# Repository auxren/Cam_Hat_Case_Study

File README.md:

# Raspberry Pi Zero 2 W Camera Module Daughterboard

## Overview

This was from a 72hr design challenge / case study for an interview for a Senior Electrical Engineering Role.

## Requirements

- Camera Module: Integrate the IMX219 camera module (IQL-IMX219/FF).
= Motion Detection: Integrate a suitable PIR motion sensor to detect motion to trigger the
camera.
- Lighting Adjustment: Integrate a suitable ambient light sensor that will be later used to
adjust camera settings based on lighting conditions.
- Power Supply: Design a power supply circuit to ensure stable operation. Choose and
justify the power management components used. Use at least one switching regulator in
your design.
- Form Factor: Ensure the daughter board fits within the dimensions of the Raspberry Pi
Zero 2 W (65mm x 30mm).
- Interconnection: The daughter board will connect to the Raspberry Pi Zero 2 W through
the GPIO header. All components, including the camera module, PIR sensor, and
ambient light sensor, must be placed on the daughter board. Additionally, include an FFC
connector on the edge of the daughter board to allow the user to connect an FFC cable
between the daughter board and the CSI interface of the Raspberry Pi Zero W.
- Power Supply: Assume the Raspberry Pi will be powered with a 5V 3A DC power
supply. Consider power losses and efficiencies.

## Features

- IMX219 camera integration via CSI interface  
- Ambient light sensor for lighting-aware imaging  
- PIR motion sensor to trigger camera events  
- Switching regulator-based power supply for high efficiency  
- Direct connection to the Raspberry Pi via GPIO and FFC  
- Test points and layout considerations for testability

## System Requirements

| Component              | Specification                                                  |
|------------------------|----------------------------------------------------------------|
| Camera Module          | IMX219 (IQL-IMX219/FF)                                         |
| PIR Sensor             | Selected for compact form factor and reliable motion detection |
| Ambient Light Sensor   | Tuned for visible spectrum and camera exposure control         |
| Power Input            | 5V 3A DC (via Raspberry Pi USB input)                          |
| Form Factor            | 65mm x 30mm (same as Raspberry Pi Zero 2 W)                    |
| Interfaces             | GPIO header and FFC connector                                  |

## Deliverables

- ✅ Schematic Design (KiCad project and PDF)
- ✅ PCB Layout (KiCad, Gerber files, and 3D model)
- ✅ Bill of Materials (BOM) with part numbers and specifications
- ✅ Power Supply Design Document (efficiency and regulator choice justification)
- ✅ Design Decision Documentation (component selection and rationale)

## Folder Structure

<pre> <code>
├── Cam_Hat_Case_Study_Oren_Levy_Presentation.key -- Case study presentation. Open in Apple Keynote.
├── Cam_Hat_Case_Study_Oren_Levy_Presentation.pdf
├── Firmware:Software
│   └── TfH_Case_Study_FW_TODO.numbers -- Document for tracking items FW should be mindful of. Open in Apple Numbers.
├── Hardware
│   ├── Block Diagram
│   │   └── Cam_Hat_Case_Study_Block_Diagram.png -- High level block diagram
│   ├── BOMs
│   │   └── Cam_Hat_Case_Study_PCB_Assembly_BOM.csv -- Assembly BOM
│   ├── Datasheets -- Datasheet PDFs for referencing
│   ├── Pinout Docs
│   │   └── Cam_Hat_Case_Study_Pinout_Tracker.numbers -- Document for tracking pinouts and net names. Open in Apple Numbers.
│   ├── Power
│   │   └── CamHat_Power_Tracker.numbers -- Power calculator document. Open in Apple Numbers.
│   ├── Schematic
│   │   └── Cam_Hat_Case_Study_Schematic.pdf
│   └── TfH_Case_Study -- KiCad Project
├── LICENSE
├── Mechanical
│   ├── Cam_Hat_Case_Study_Model.STEP -- Model of full "product"
│   ├── Cam_Hat_Case_Study_Ortho_Render.png
│   ├── Cam_Hat_Case_Study_Render_Case_Ortho.png
│   ├── Cam_Hat_Case_Study_Side_Render.png
│   └── Subassemblies  -- Folder with dxf and stp files used for assembly
└── README.md
</code> </pre>

## Block Diagram

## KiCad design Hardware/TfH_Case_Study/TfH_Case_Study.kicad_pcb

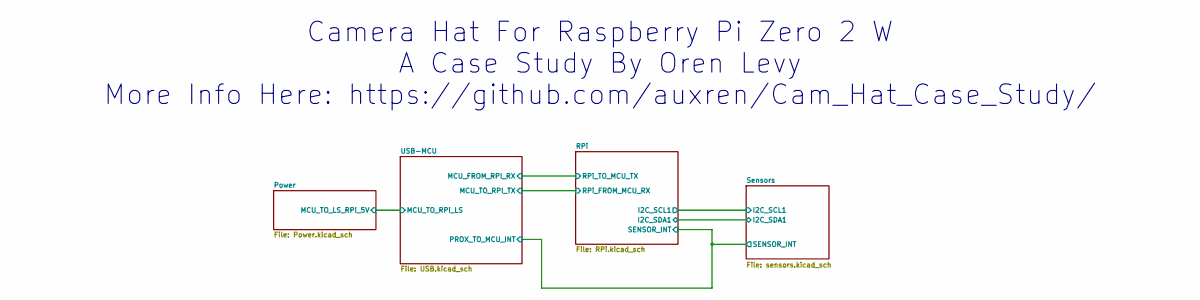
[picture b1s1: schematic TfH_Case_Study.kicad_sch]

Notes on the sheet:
Camera Hat For Raspberry Pi Zero 2 W A Case Study By Oren Levy More Info Here: https://github.com/auxren/Cam_Hat_Case_Study/

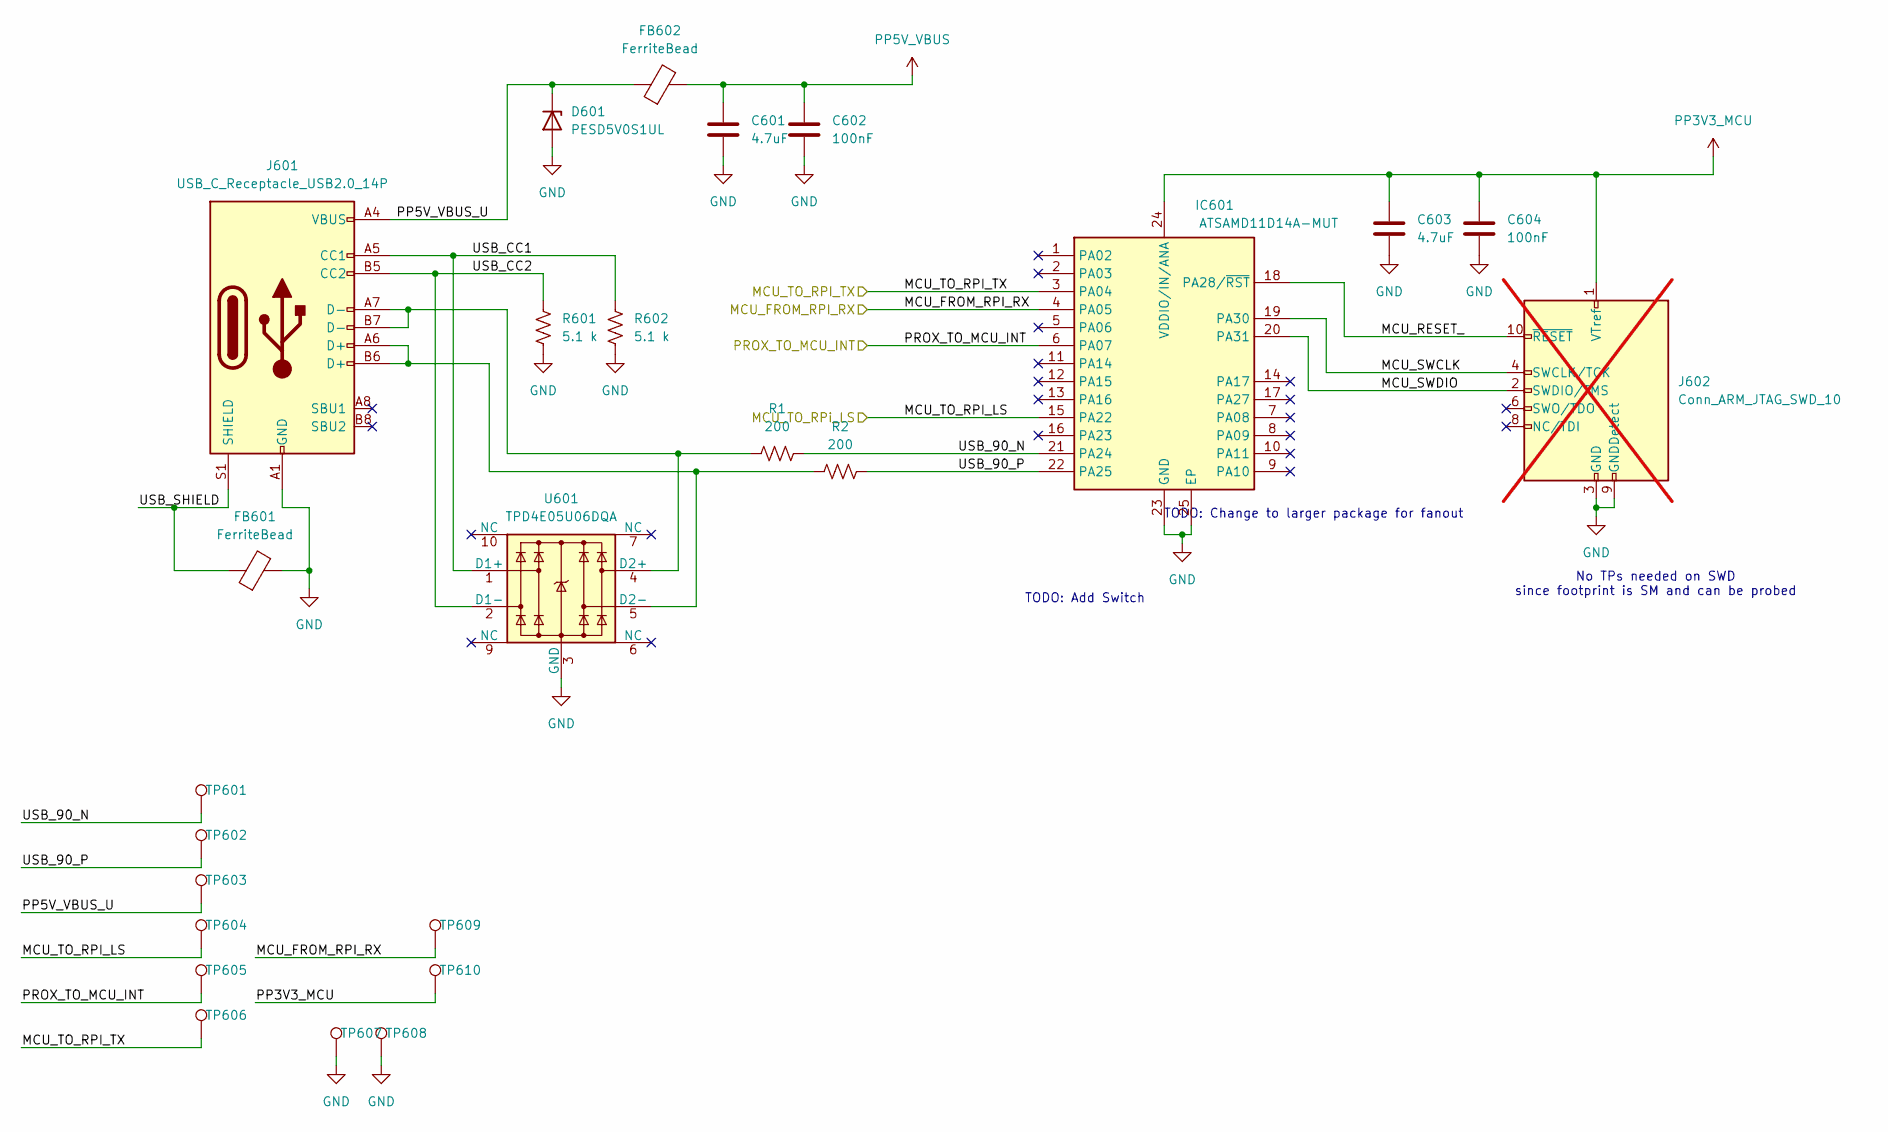
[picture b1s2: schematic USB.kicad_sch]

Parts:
C601, C603: 4.7uF; C_0402_1005Metric
C602, C604: 100nF; C_0402_1005Metric
D601: PESD5V0S1UL; D_SOD-882
FB601, FB602: FerriteBead; C_0402_1005Metric
IC601: ATSAMD11D14A-MUT; QFN50P400X400X90-25N-D; Mouser Part Number 556-ATSAMD11D14A-MUT
J601: USB_C_Receptacle_USB2.0_14P; USB_C_Receptacle_GCT_USB4105-xx-A_16P_TopMnt_Horizontal
J602: Conn_ARM_JTAG_SWD_10; PinHeader_2x05_P1.00mm_Vertical_SMD; not fitted
R1, R2: 200; R_0402_1005Metric
R601, R602: 5.1 k; R_0402_1005Metric
TP601, TP602, TP603, TP604, TP605, TP606, TP607, TP608, TP609, TP610: TestPoint; TestPoint_Pad_D1.5mm
U601: TPD4E05U06DQA; USON-10_2.5x1.0mm_P0.5mm

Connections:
/Sensors/SENSOR_INT: IC601.6 (PA07), TP605.1; also elsewhere on the board
/USB-MCU/MCU_FROM_RPI_RX: IC601.4 (PA05), TP609.1; also elsewhere on the board
/USB-MCU/MCU_RESET_: IC601.18 (PA28/~RST), J602.10 (~RESET)
/USB-MCU/MCU_SWCLK: IC601.19 (PA30), J602.4 (SWCLK/TCK)
/USB-MCU/MCU_SWDIO: IC601.20 (PA31), J602.2 (SWDIO/TMS)
/USB-MCU/MCU_TO_RPI_LS: IC601.15 (PA22), TP604.1; also elsewhere on the board
/USB-MCU/MCU_TO_RPI_TX: IC601.3 (PA04), TP606.1; also elsewhere on the board
/USB-MCU/PP5V_VBUS_U: D601.1 (K), FB602.1, J601.A4 (VBUS), J601.A9 (VBUS), J601.B4 (VBUS), J601.B9 (VBUS), TP603.1
/USB-MCU/USB_CC1: J601.A5 (CC1), R602.1, U601.1 (D1+)
/USB-MCU/USB_CC2: J601.B5 (CC2), R601.1, U601.2 (D1-)
/USB-MCU/USB_SHIELD: FB601.1, J601.S1 (SHIELD)
GND: C601.2, C602.2, C603.2, C604.2, D601.2 (A), FB601.2, IC601.23 (GND), IC601.25 (EP), J601.A1 (GND), J601.A12 (GND), J601.B1 (GND), J601.B12 (GND), J602.3 (GND), J602.5 (GND), J602.9 (GNDDetect), R601.2, R602.2, TP607.1, TP608.1, U601.3 (GND), U601.8 (GND); also elsewhere on the board
PP3V3_MCU: C603.1, C604.1, IC601.24 (VDDIO/IN/ANA), J602.1 (VTref), TP610.1; also elsewhere on the board
PP5V_VBUS: C601.1, C602.1, FB602.2; also elsewhere on the board

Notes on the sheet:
No TPs needed on SWD since footprint is SM and can be probed
TODO: Change to larger package for fanout
TODO: Add Switch

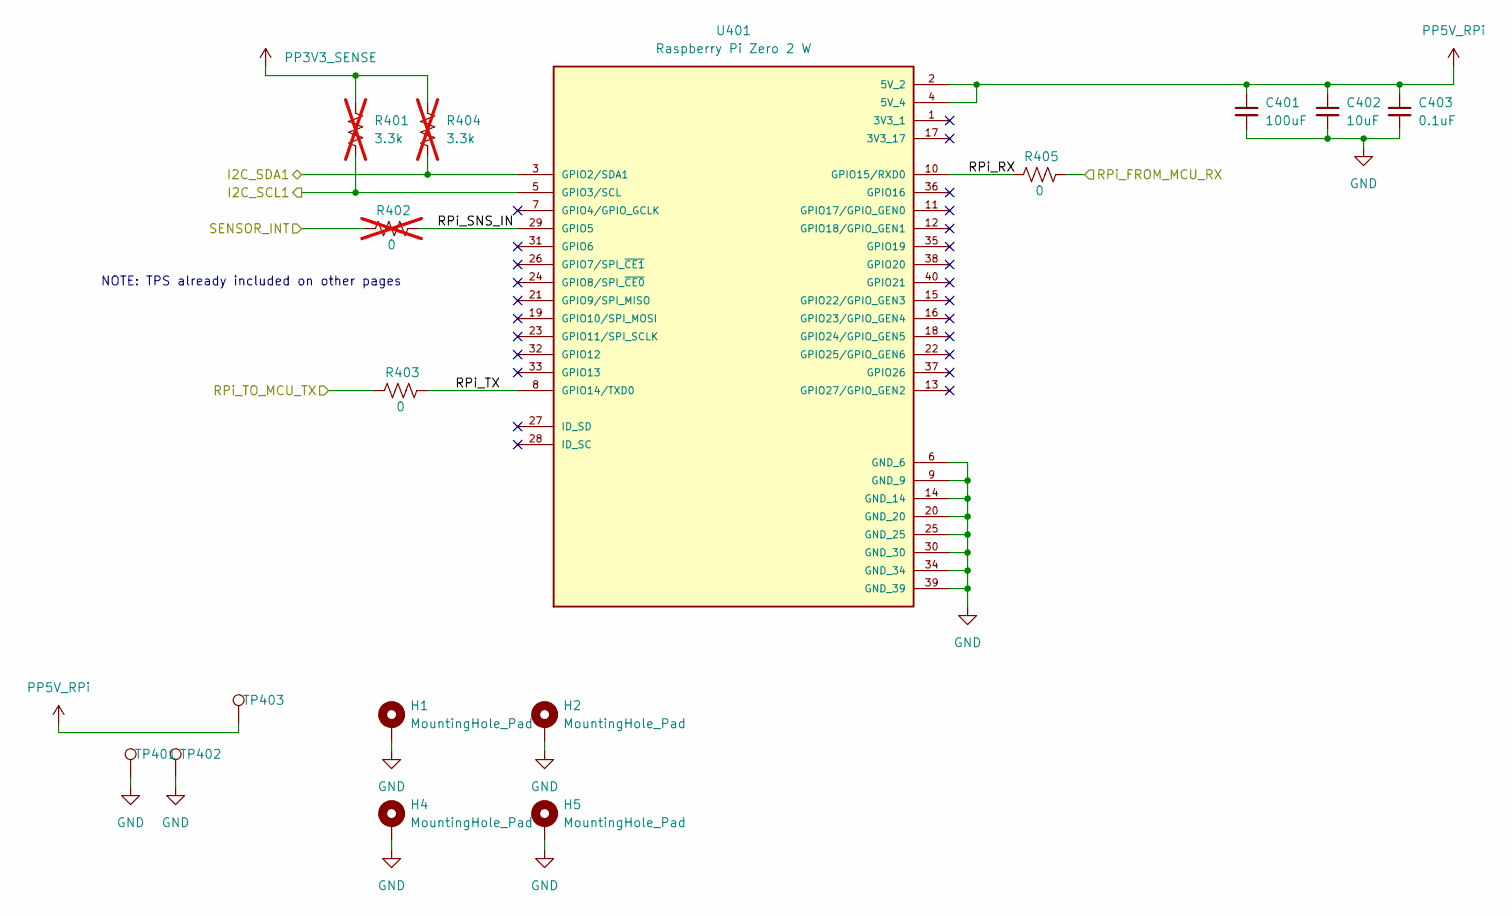
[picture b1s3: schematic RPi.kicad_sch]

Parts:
C401: 100uF; C_0603_1608Metric
C402: 10uF; C_0603_1608Metric
C403: 0.1uF; C_0402_1005Metric
H1, H2, H4, H5: MountingHole_Pad; MountingHole_3.2mm_M3_DIN965_Pad
R401, R404: 3.3k; C_0402_1005Metric; not fitted
R402: 0; C_0402_1005Metric; not fitted
R403, R405: 0; C_0402_1005Metric
TP401, TP402, TP403: TestPoint; TestPoint_Pad_D1.5mm
U401: Raspberry Pi Zero 2 W; PinHeader_2x20_P2.54mm_Vertical; PARTREV April 2024

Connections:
/RPi/RPi_RX: R405.1, U401.10 (GPIO15/RXD0)
/RPi/RPi_SNS_IN: R402.2, U401.29 (GPIO5)
/RPi/RPi_TX: R403.2, U401.8 (GPIO14/TXD0)
/Sensors/I2C_SCL1: R401.2, U401.5 (GPIO3/SCL); also elsewhere on the board
/Sensors/I2C_SDA1: R404.2, U401.3 (GPIO2/SDA1); also elsewhere on the board
/Sensors/SENSOR_INT: R402.1; also elsewhere on the board
/USB-MCU/MCU_FROM_RPI_RX: R403.1; also elsewhere on the board
/USB-MCU/MCU_TO_RPI_TX: R405.2; also elsewhere on the board
GND: C401.2, C402.2, C403.2, H1.1, H2.1, H4.1, H5.1, TP401.1, TP402.1, U401.6 (GND_6), U401.9 (GND_9), U401.14 (GND_14), U401.20 (GND_20), U401.25 (GND_25), U401.30 (GND_30), U401.34 (GND_34), U401.39 (GND_39); also elsewhere on the board
PP3V3_SENSE: R401.1, R404.1; also elsewhere on the board
PP5V_RPi: C401.1, C402.1, C403.1, TP403.1, U401.2 (5V_2), U401.4 (5V_4); also elsewhere on the board

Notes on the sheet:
NOTE: TPS already included on other pages

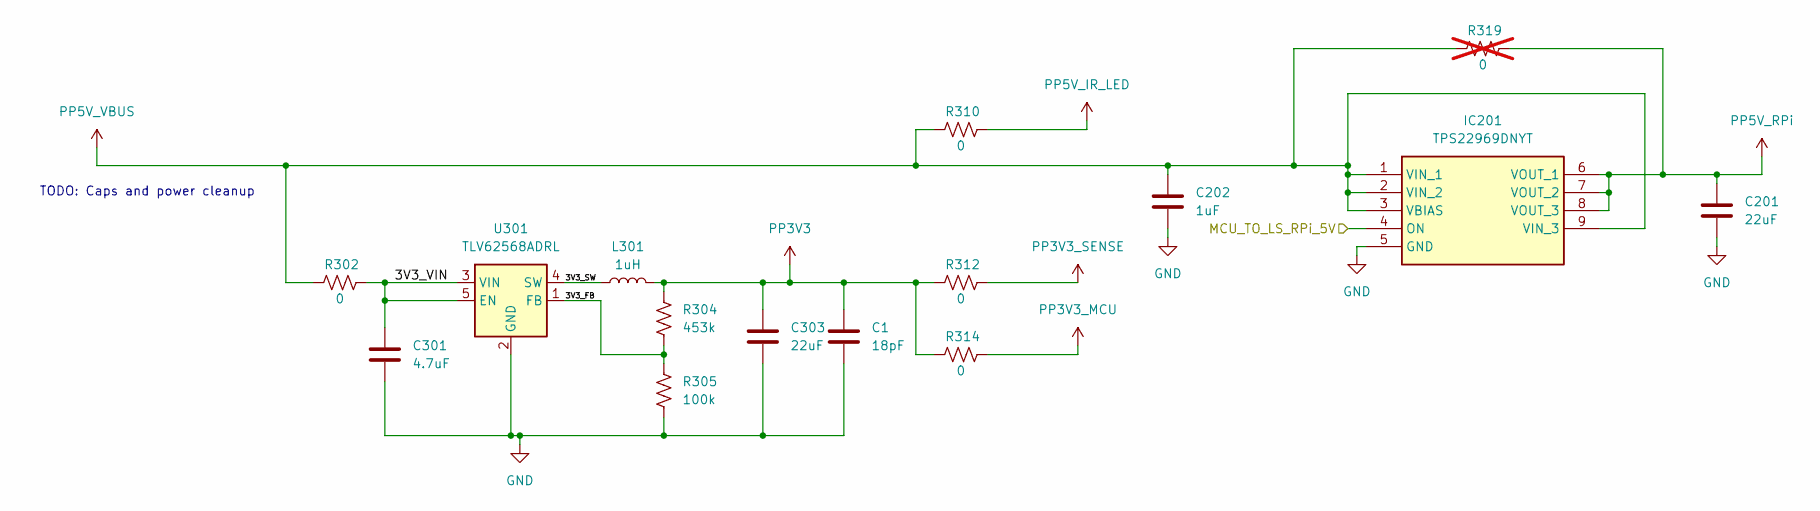
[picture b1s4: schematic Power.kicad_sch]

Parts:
C1: 18pF; C_0402_1005Metric
C201, C303: 22uF; C_0402_1005Metric
C202: 1uF; C_0402_1005Metric
C301: 4.7uF; C_0402_1005Metric
IC201: TPS22969DNYT; Mouser Part Number 595-TPS22969DNYT
L301: 1uH; C_0402_1005Metric
R302, R310, R312, R314: 0; C_0402_1005Metric
R304: 453k; C_0402_1005Metric
R305: 100k; C_0402_1005Metric
R319: 0; C_0402_1005Metric; not fitted
U301: TLV62568ADRL; SOT-563

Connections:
/Power/3V3_FB: R304.2, R305.1, U301.1 (FB)
/Power/3V3_SW: L301.1, U301.4 (SW)
/Power/3V3_VIN: C301.1, R302.2, U301.3 (VIN), U301.5 (EN)
/USB-MCU/MCU_TO_RPI_LS: IC201.4 (ON); also elsewhere on the board
GND: C1.2, C201.2, C202.2, C301.2, C303.2, IC201.5 (GND), R305.2, U301.2 (GND); also elsewhere on the board
PP3V3: C1.1, C303.1, L301.2, R304.1, R312.1, R314.1
PP3V3_MCU: R314.2; also elsewhere on the board
PP3V3_SENSE: R312.2; also elsewhere on the board
PP5V_IR_LED: R310.2; also elsewhere on the board
PP5V_RPi: C201.1, IC201.6 (VOUT_1), IC201.7 (VOUT_2), IC201.8 (VOUT_3), R319.2; also elsewhere on the board
PP5V_VBUS: C202.1, IC201.1 (VIN_1), IC201.2 (VIN_2), IC201.3 (VBIAS), IC201.9 (VIN_3), R302.1, R310.1, R319.1; also elsewhere on the board

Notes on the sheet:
TODO: Caps and power cleanup

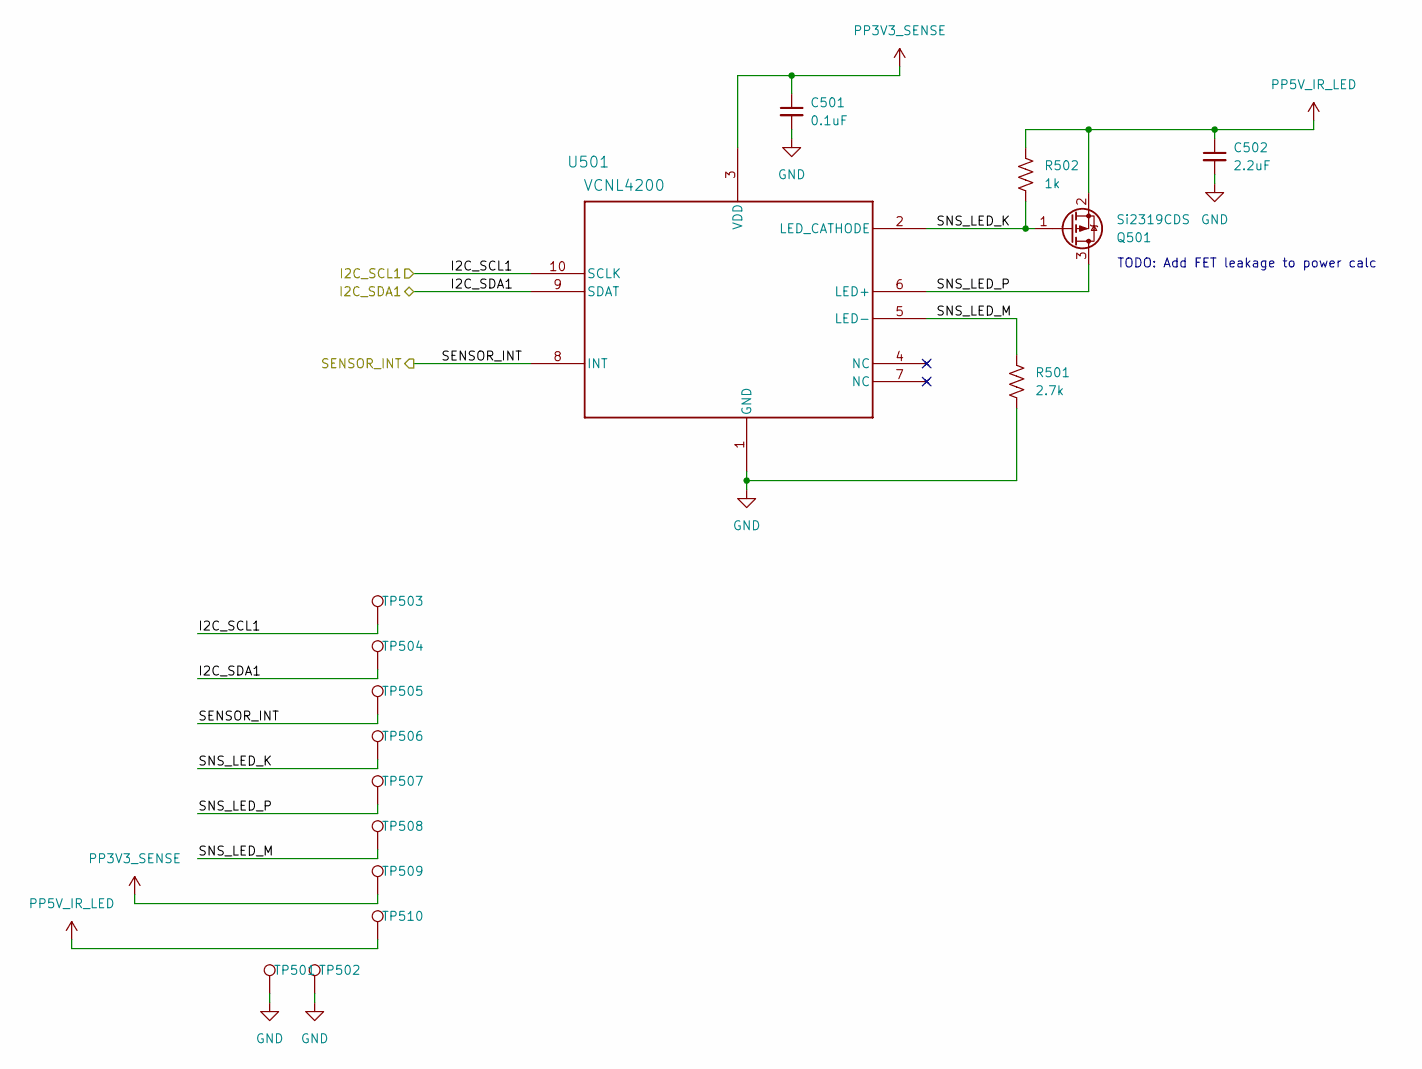
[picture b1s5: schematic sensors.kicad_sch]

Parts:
C501: 0.1uF; C_0402_1005Metric
C502: 2.2uF; C_0402_1005Metric
Q501: Si2319CDS; SOT-23
R501: 2.7k; R_0402_1005Metric
R502: 1k; R_0402_1005Metric
TP501, TP502, TP503, TP504, TP505, TP506, TP507, TP508, TP509, TP510: TestPoint; TestPoint_Pad_D1.5mm
U501: VCNL4200; SMT_L4200_VIS

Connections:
/Sensors/I2C_SCL1: TP503.1, U501.10 (SCLK); also elsewhere on the board
/Sensors/I2C_SDA1: TP504.1, U501.9 (SDAT); also elsewhere on the board
/Sensors/SENSOR_INT: TP505.1, U501.8 (INT); also elsewhere on the board
/Sensors/SNS_LED_K: Q501.1 (G), R502.2, TP506.1, U501.2 (LED_CATHODE)
/Sensors/SNS_LED_M: R501.1, TP508.1, U501.5 (LED-)
/Sensors/SNS_LED_P: Q501.3 (D), TP507.1, U501.6 (LED+)
GND: C501.2, C502.2, R501.2, TP501.1, TP502.1, U501.1 (GND); also elsewhere on the board
PP3V3_SENSE: C501.1, TP509.1, U501.3 (VDD); also elsewhere on the board
PP5V_IR_LED: C502.1, Q501.2 (S), R502.1, TP510.1; also elsewhere on the board

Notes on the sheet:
TODO: Add FET leakage to power calc

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
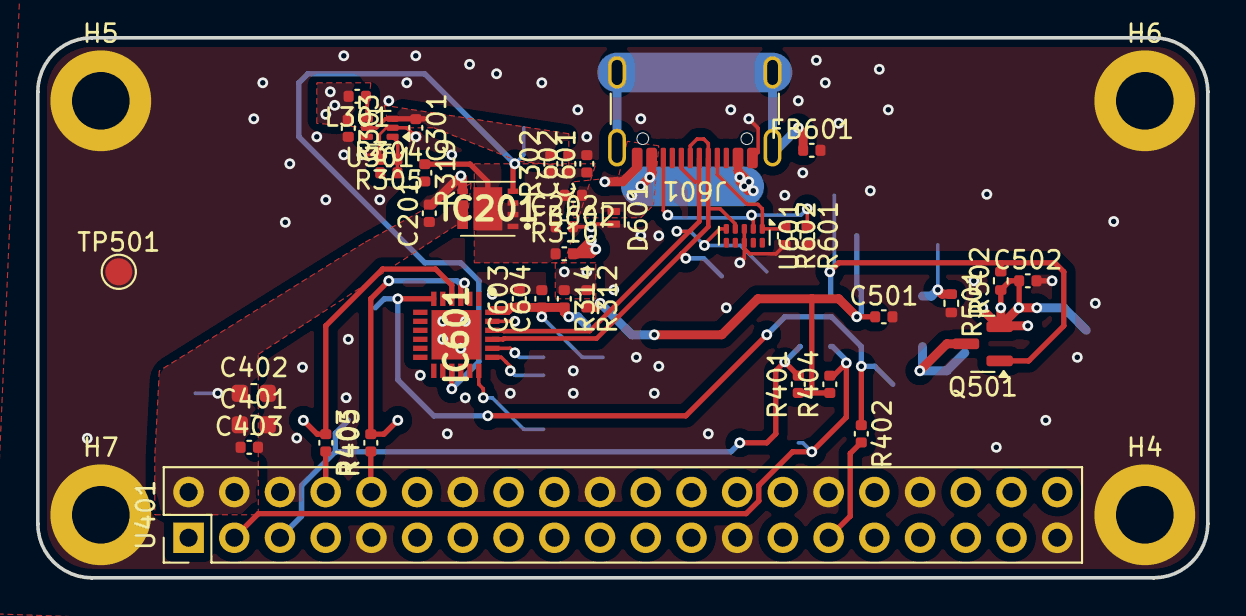
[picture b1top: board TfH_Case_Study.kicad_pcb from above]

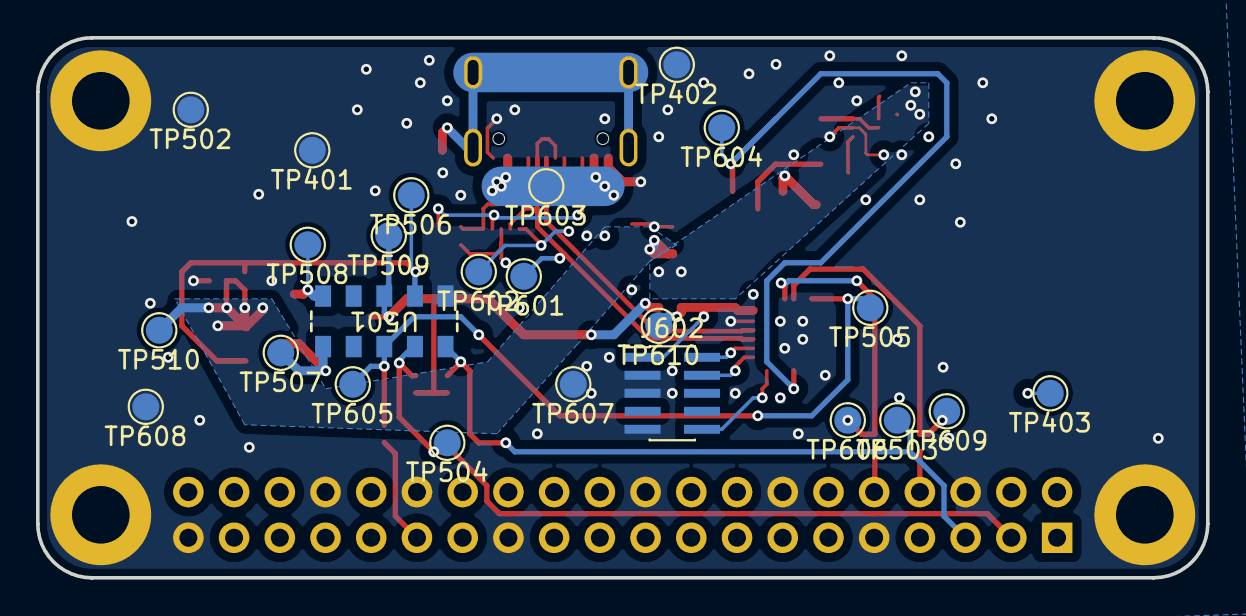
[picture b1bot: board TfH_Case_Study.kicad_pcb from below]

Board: 2 copper layers, 65.0 x 30.0 mm, 69 parts (24 on the bottom side), 31 nets.

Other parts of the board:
H6, H7: MountingHole_Pad; MountingHole_3.2mm_M3_DIN965_Pad

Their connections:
GND: H6.1, H7.1; also elsewhere on the board

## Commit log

2025-06-09 Initial Commit
    Setting Up Files and Folder Structures
2025-06-10 Daily Checkin - Schematic In progress
    Camera and Sensor pages nearly done
2025-06-10 Power Tracker Added
    Added components to power schematic page
2025-06-11 Placement Started
    Lots of TODOs in Schematic
    Started placement
2025-06-11 Before Finding The Eagle Board
2025-06-12 Pencils Down For PCBA
2025-06-12 Updated Documentation
2025-06-12 BOM Not Showing Up Fix?
2025-06-12 GitIgnore Fix
2025-06-12 Updated Presentation And Generated PDF
2025-06-23 Cleanup And Post Final
    Done with this project
